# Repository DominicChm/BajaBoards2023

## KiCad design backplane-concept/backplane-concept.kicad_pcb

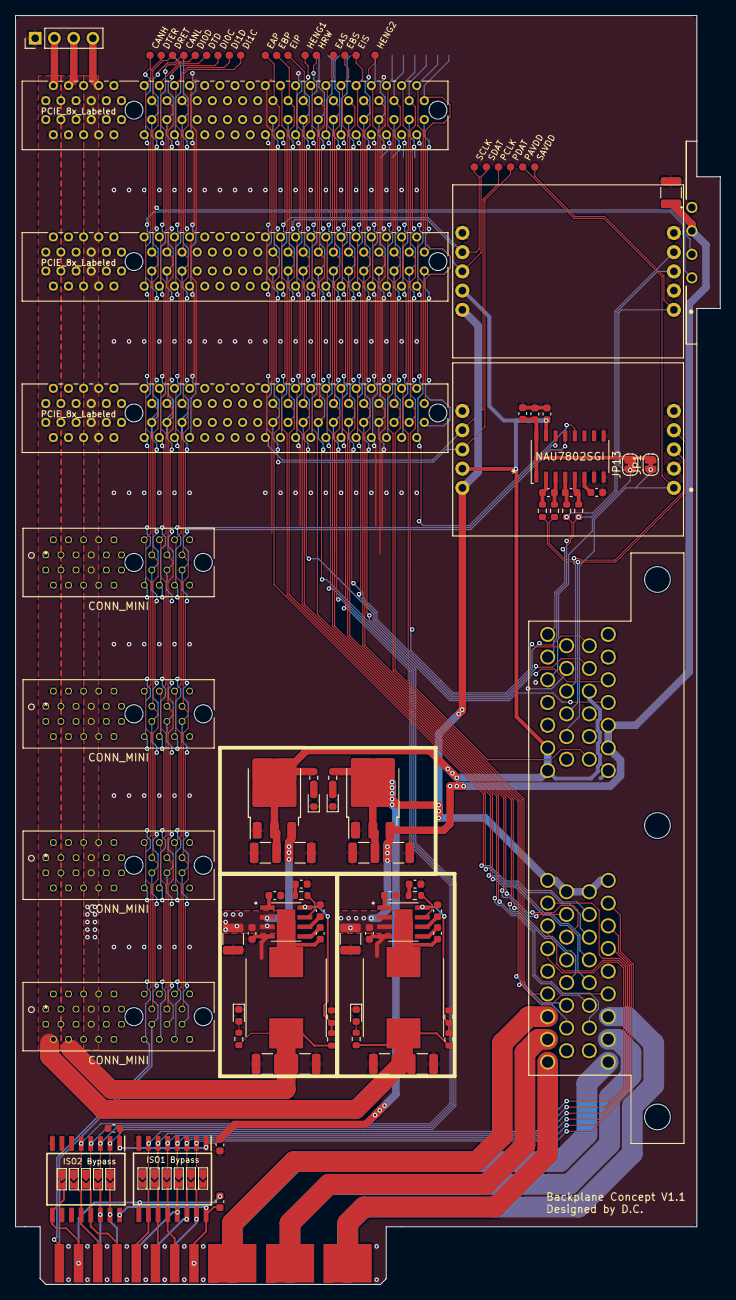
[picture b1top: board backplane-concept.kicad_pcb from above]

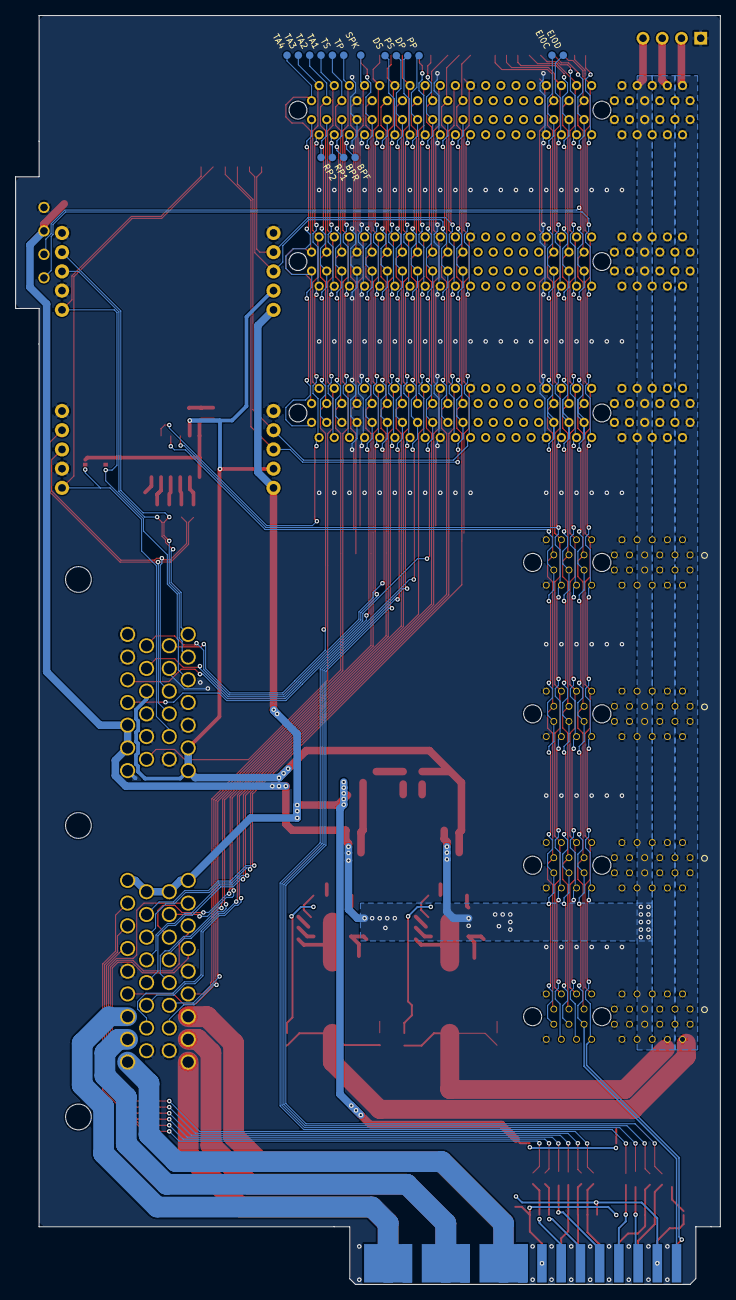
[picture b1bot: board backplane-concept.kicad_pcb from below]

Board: 2 copper layers, 93.1 x 167.6 mm, 124 parts (18 on the bottom side), 109 nets.

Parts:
C1, C3, C16, C21: 1uF; C_0603_1608Metric
C2, C4, C5, C6, C13, C22, C25, C26, C28, C29, C31: 0.1uF; C_0603_1608Metric
C7, C8, C9, C10, C12, C14, C15, C18, C23, C24, C27: 22uF; C_1210_3225Metric
C11, C20: 47nF; C_0603_1608Metric
C17, C19: 1.8nF; C_0603_1608Metric
D1: 3V3A; LED_0603_1608Metric
D2: 5VA; LED_0603_1608Metric
D3: 5V; LED_0603_1608Metric
D4: 3V3; LED_0603_1608Metric
IC1, IC2: ISO6760DWR; SOIC127P1030X265-16N
J1: ECVT I/O; 64734271
J2, J3, J4: PCIE_8x_Labeled; 9-1734774-5
J5, J6, J7, J8: CONN_MINI; 10018784-10200TLF
J10: 5-5530843-3-EDGE
J11: 1-967657-1; 19676571
J12: POWER; PinHeader_1x04_P2.54mm_Vertical
JP1: AVDD_P; SolderJumper-2_P1.3mm_Bridged_RoundedPad1.0x1.5mm
JP2, JP3, JP4, JP5, JP6, JP7, JP8, JP9, JP10, JP11, JP12: SolderJumper_2_Open; JMP_Small
JP13: AVDD_S; SolderJumper-2_P1.3mm_Bridged_RoundedPad1.0x1.5mm
L1, L2: 3.8uH; L_Taiyo-Yuden_NR-10050_9.8x10.0mm_HandSoldering
R1, R2, R3, R4: 47; R_0603_1608Metric
R5: 14.7K; R_0603_1608Metric
R6: 110K; R_0603_1608Metric
R7, R10: 15K; R_0603_1608Metric
R8: 10K; R_0603_1608Metric
R9: 67.5K; R_0603_1608Metric
R12, R15: 130; R_0603_1608Metric
R13, R14: 300; R_0603_1608Metric
TP1: PCLK; TestPoint_Pad_D1.0mm
TP2: PDAT; TestPoint_Pad_D1.0mm
TP3: SCLK; TestPoint_Pad_D1.0mm
TP4: SDAT; TestPoint_Pad_D1.0mm
TP5: SAVDD; TestPoint_Pad_D1.0mm
TP6: PAVDD; TestPoint_Pad_D1.0mm
TP12: HENG1; TestPoint_Pad_D1.0mm
TP13: HENG2; TestPoint_Pad_D1.0mm
TP14: BPF; TestPoint_Pad_D1.0mm
TP15: BPR; TestPoint_Pad_D1.0mm
TP16: RP1; TestPoint_Pad_D1.0mm
TP17: RP2; TestPoint_Pad_D1.0mm
TP18: HRW; TestPoint_Pad_D1.0mm
TP19: PP; TestPoint_Pad_D1.0mm
TP20: DP; TestPoint_Pad_D1.0mm
TP21: PS; TestPoint_Pad_D1.0mm
TP22: DS; TestPoint_Pad_D1.0mm
TP23: TP; TestPoint_Pad_D1.0mm
TP24: TS; TestPoint_Pad_D1.0mm
TP25: TA1; TestPoint_Pad_D1.0mm
TP26: TA2; TestPoint_Pad_D1.0mm
TP27: TA3; TestPoint_Pad_D1.0mm
TP28: TA4; TestPoint_Pad_D1.0mm
TP29: SPK; TestPoint_Pad_D1.0mm
TP30: EAS; TestPoint_Pad_D1.0mm
TP31: EBS; TestPoint_Pad_D1.0mm
TP32: EIS; TestPoint_Pad_D1.0mm
TP33: EAP; TestPoint_Pad_D1.0mm
TP34: EBP; TestPoint_Pad_D1.0mm
TP35: EIP; TestPoint_Pad_D1.0mm
TP36: DI1C; TestPoint_Pad_D1.0mm
TP37: DI1D; TestPoint_Pad_D1.0mm
TP38: DI0D; TestPoint_Pad_D1.0mm
TP39: DI0C; TestPoint_Pad_D1.0mm
TP40: CANH; TestPoint_Pad_D1.0mm
TP41: CANL; TestPoint_Pad_D1.0mm
TP42: EI0D; TestPoint_Pad_D1.0mm
TP43: EI0C; TestPoint_Pad_D1.0mm
TP44: DRET; TestPoint_Pad_D1.0mm
TP45: DTD; TestPoint_Pad_D1.0mm
TP46: DTER; TestPoint_Pad_D1.0mm
U1: PRIMARY; SPARKFUN_SEN-13879
U2: SECONDARY; SPARKFUN_SEN-13879
U3: NAU7802SGI
U6: 5V Reg; AOZ6605PI-1
U7: AMS1117CD-5.0; TO-252-3_TabPin2
U8: 3.3V Reg; AOZ6605PI-1
U9: AMS1117CD-3.3; TO-252-3_TabPin2

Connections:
+3.3VA: C1.1, C10.1, J1.B10, J1.B25, J1.B26, R12.1, U1.9 (VCC), U2.9 (VCC), U3.15 (DVDD), U9.2 (VO)
+3V3: C23.1, C24.1, J2.A4 (+3V3), J2.A5 (+3V3), J2.A6 (+3V3), J2.B4 (+3V3), J2.B5 (+3V3), J2.B6 (+3V3), J3.A4 (+3V3), J3.A5 (+3V3), J3.A6 (+3V3), J3.B4 (+3V3), J3.B5 (+3V3), J3.B6 (+3V3), J4.A4 (+3V3), J4.A5 (+3V3), J4.A6 (+3V3), J4.B4 (+3V3), J4.B5 (+3V3), J4.B6 (+3V3), J5.A4 (+3V3), J5.A5 (+3V3), J5.A6 (+3V3), J5.B4 (+3V3), J5.B5 (+3V3), J5.B6 (+3V3), J6.A4 (+3V3), J6.A5 (+3V3), J6.A6 (+3V3), J6.B4 (+3V3), J6.B5 (+3V3), J6.B6 (+3V3), J7.A4 (+3V3), J7.A5 (+3V3), J7.A6 (+3V3), J7.B4 (+3V3), J7.B5 (+3V3), J7.B6 (+3V3), J8.A4 (+3V3), J8.A5 (+3V3), J8.A6 (+3V3), J8.B4 (+3V3), J8.B5 (+3V3), J8.B6 (+3V3), J12.3, L2.2, R9.1, R15.1
+5V: C14.1, C15.1, J2.A1 (+5V), J2.A2 (+5V), J2.A3 (+5V), J2.B1 (+5V), J2.B2 (+5V), J2.B3 (+5V), J3.A1 (+5V), J3.A2 (+5V), J3.A3 (+5V), J3.B1 (+5V), J3.B2 (+5V), J3.B3 (+5V), J4.A1 (+5V), J4.A2 (+5V), J4.A3 (+5V), J4.B1 (+5V), J4.B2 (+5V), J4.B3 (+5V), J5.A1 (+5V), J5.A2 (+5V), J5.A3 (+5V), J5.B1 (+5V), J5.B2 (+5V), J5.B3 (+5V), J6.A1 (+5V), J6.A2 (+5V), J6.A3 (+5V), J6.B1 (+5V), J6.B2 (+5V), J6.B3 (+5V), J7.A1 (+5V), J7.A2 (+5V), J7.A3 (+5V), J7.B1 (+5V), J7.B2 (+5V), J7.B3 (+5V), J8.A1 (+5V), J8.A2 (+5V), J8.A3 (+5V), J8.B1 (+5V), J8.B2 (+5V), J8.B3 (+5V), J12.2, L1.2, R6.1, R14.1
+5VA: C8.1, C28.1, C31.1, IC1.1 (VCC1), IC2.1 (VCC1), J1.A1, J1.A10, J1.A18, J1.A26, R13.1, U1.10 (VDD), U2.10 (VDD), U7.2 (VO)
+8V: C7.1, C9.1, C12.1, C18.1, C25.1, C26.1, C27.1, J1.B5, J1.B6, J2.A7 (VBATT), J2.A8 (VBATT), J2.B7 (VBATT), J2.B8 (VBATT), J3.A7 (VBATT), J3.A8 (VBATT), J3.B7 (VBATT), J3.B8 (VBATT), J4.A7 (VBATT), J4.A8 (VBATT), J4.B7 (VBATT), J4.B8 (VBATT), J5.A7 (VBATT), J5.A8 (VBATT), J5.B7 (VBATT), J5.B8 (VBATT), J6.A7 (VBATT), J6.A8 (VBATT), J6.B7 (VBATT), J6.B8 (VBATT), J7.A7 (VBATT), J7.A8 (VBATT), J7.B7 (VBATT), J7.B8 (VBATT), J8.A7 (VBATT), J8.A8 (VBATT), J8.B7 (VBATT), J8.B8 (VBATT), J11.2 (VBATT), J12.4, U6.2 (EN), U6.3 (VIN), U7.3 (VI), U8.2 (EN), U8.3 (VIN), U9.3 (VI)
/DIR_P_ISO: IC2.14 (OUTB), J10.A15 (PWM_P), JP10.2 (B)
/DIR_S_ISO: IC2.12 (OUTD), J10.B15 (PWM_S), JP12.2 (B)
/HALL1_P_ISO: IC1.15 (OUTA), J10.A11 (HALL1_P), JP2.2 (B)
/HALL1_S_ISO: IC1.12 (OUTD), J10.B11 (HALL1_S), JP5.2 (B)
/HALL2_P_ISO: IC1.14 (OUTB), J10.A12 (HALL2_P), JP3.2 (B)
/HALL2_S_ISO: IC1.11 (OUTE), J10.B12 (HALL2_S), JP6.2 (B)
/HALL3_P_ISO: IC1.13 (OUTC), J10.A13 (HALL3_P), JP4.2 (B)
/HALL3_S_ISO: IC1.10 (OUTF), J10.B13 (HALL3_S), JP7.2 (B)
/PWM_P_ISO: IC2.15 (OUTA), J10.A14 (DIR_P), JP9.2 (B)
/PWM_S_ISO: IC2.13 (OUTC), J10.B14 (DIR_S), JP11.2 (B)
/VDD_ISO: C29.1, IC1.16 (VCC2), IC2.16 (VCC2), J10.A10 (VDD), J10.B10 (VDD)
/VSS_ISO: C29.2, IC1.9 (GND2), IC2.9 (GND2), J10.A16 (VSS), J10.B16 (VSS), JP8.2 (B)
ADC_IRQ: J2.B48, J3.B48, J4.B48, U3.12 (DRDY)
AVDD_P: J1.B18, JP1.1 (A), TP6.1, U1.1 (RED)
AVDD_S: J1.B22, JP13.1 (A), TP5.1, U2.1 (RED)
BP_FRONT: J2.B44 (BP_FRONT), J3.B44 (BP_FRONT), J4.B44 (BP_FRONT), TP14.1
BP_REAR: J2.B45 (BP_REAR), J3.B45 (BP_REAR), J4.B45 (BP_REAR), TP15.1
CAN_H: J2.B12 (CAN_H), J3.B12 (CAN_H), J4.B12 (CAN_H), J5.B12 (CAN_H), J6.B12 (CAN_H), J7.B12 (CAN_H), J8.B12 (CAN_H), J10.B17 (CANH), J11.4 (CANH), TP40.1
CAN_L: J2.B13 (CAN_L), J3.B13 (CAN_L), J4.B13 (CAN_L), J5.B13 (CAN_L), J6.B13 (CAN_L), J7.B13 (CAN_L), J8.B13 (CAN_L), J10.A17 (CANL), J11.3 (CANL), TP41.1
DAQ_RX0_ECVT_TX0: J2.A13 (DAQ_RX0_ECVT_TX0), J3.A13 (DAQ_RX0_ECVT_TX0), J4.A13 (DAQ_RX0_ECVT_TX0), J5.A13 (DAQ_RX0_ECVT_TX0), J6.A13 (DAQ_RX0_ECVT_TX0), J7.A13 (DAQ_RX0_ECVT_TX0), J8.A13 (DAQ_RX0_ECVT_TX0), TP44.1
DAQ_TX0_ECVT_RX0: J2.A12 (DAQ_TX0_ECVT_RX0), J3.A12 (DAQ_TX0_ECVT_RX0), J4.A12 (DAQ_TX0_ECVT_RX0), J5.A12 (DAQ_TX0_ECVT_RX0), J6.A12 (DAQ_TX0_ECVT_RX0), J7.A12 (DAQ_TX0_ECVT_RX0), J8.A12 (DAQ_TX0_ECVT_RX0), TP46.1
DAQ_TX1_DATA: J2.A14 (DAQ_TX1_DATA), J3.A14 (DAQ_TX1_DATA), J4.A14 (DAQ_TX1_DATA), J5.A14 (DAQ_TX1_DATA), J6.A14 (DAQ_TX1_DATA), J7.A14 (DAQ_TX1_DATA), J8.A14 (DAQ_TX1_DATA), TP45.1
DIR_P: IC2.3 (INB), J2.B36 (DIR_P), J3.B36 (DIR_P), J4.B36 (DIR_P), JP10.1 (A), TP20.1
DIR_S: IC2.5 (IND), J2.B38 (DIR_S), J3.B38 (DIR_S), J4.B38 (DIR_S), JP12.1 (A), TP22.1
ENCA_P: J1.A11, J2.A29 (ENCA_P), J3.A29 (ENCA_P), J4.A29 (ENCA_P), TP33.1
ENCA_S: J1.A19, J2.A36 (ENCA_S), J3.A36 (ENCA_S), J4.A36 (ENCA_S), TP30.1
ENCB_P: J1.A13, J2.A31 (ENCB_P), J3.A31 (ENCB_P), J4.A31 (ENCB_P), TP34.1
ENCB_S: J1.A21, J2.A38 (ENCB_S), J3.A38 (ENCB_S), J4.A38 (ENCB_S), TP31.1
ENCI_P: J1.A15, J2.A33 (ENCI_P), J3.A33 (ENCI_P), J4.A33 (ENCI_P), TP35.1
ENCI_S: J1.A23, J2.A40 (ENCI_S), J3.A40 (ENCI_S), J4.A40 (ENCI_S), TP32.1
GND: C1.2, C2.2, C3.2, C6.2, C7.2, C8.2, C9.2, C10.2, C11.2, C12.2, C14.2, C15.2, C16.2, C17.2, C18.2, C19.2, C20.2, C21.2, C23.2, C24.2, C25.2, C26.2, C27.2, C28.2, C31.2, D1.1 (K), D2.1 (K), D3.1 (K), D4.1 (K), IC1.8 (GND1), IC2.8 (GND1), J1.A5, J1.A17, J1.A25, J1.A30, J1.B1, J1.B2, J1.B7, J1.B11, J1.B12, J1.B15, J1.B19, J1.B23, J1.B24, J2.A9 (GND), J2.A10 (GND), J2.A11 (GND), J2.A15 (GND), J2.A18 (GND), J2.A28 (GND), J2.A35 (GND), J2.A43 (GND), J2.B9 (GND), J2.B10 (GND), J2.B11 (GND), J2.B18 (GND), J2.B32 (GND), J2.B42 (GND), J2.B43 (GND), J3.A9 (GND), J3.A10 (GND), J3.A11 (GND), J3.A15 (GND), J3.A18 (GND), J3.A28 (GND), J3.A35 (GND), J3.A43 (GND), J3.B9 (GND), J3.B10 (GND), J3.B11 (GND), J3.B18 (GND), J3.B32 (GND), J3.B42 (GND), J3.B43 (GND), J4.A9 (GND), J4.A10 (GND), J4.A11 (GND), J4.A15 (GND), J4.A18 (GND), J4.A28 (GND), J4.A35 (GND), J4.A43 (GND), J4.B9 (GND), J4.B10 (GND), J4.B11 (GND), J4.B18 (GND), J4.B32 (GND), J4.B42 (GND), J4.B43 (GND), J5.A9 (GND), J5.A10 (GND), J5.A11 (GND), J5.A15 (GND), J5.A18 (GND), J5.B9 (GND), J5.B10 (GND), J5.B11 (GND), J5.B18 (GND), J6.A9 (GND), J6.A10 (GND), J6.A11 (GND), J6.A15 (GND), J6.A18 (GND), J6.B9 (GND), J6.B10 (GND), J6.B11 (GND), J6.B18 (GND), J7.A9 (GND), J7.A10 (GND), J7.A11 (GND), J7.A15 (GND), J7.A18 (GND), J7.B9 (GND), J7.B10 (GND), J7.B11 (GND), J7.B18 (GND), J8.A9 (GND), J8.A10 (GND), J8.A11 (GND), J8.A15 (GND), J8.A18 (GND), J8.B9 (GND), J8.B10 (GND), J8.B11 (GND), J8.B18 (GND), J11.1 (GND), J12.1, JP8.1 (A), R7.2, R10.2, U1.2 (BLK), U1.5 (YLW), U1.6 (GND), U2.2 (BLK), U2.5 (YLW), U2.6 (GND), U3.7 (REFN), U3.8 (AVSS), U3.9 (DVSS), U6.4 (GND), U7.1 (GND), U8.4 (GND), U9.1 (GND)
HALL1_P: IC1.2 (INA), J1.A2, JP2.1 (A)
HALL1_S: IC1.5 (IND), J1.A27, JP5.1 (A)
HALL2_P: IC1.3 (INB), J1.A3, JP3.1 (A)
HALL2_S: IC1.6 (INE), J1.A28, JP6.1 (A)
HALL3_P: IC1.4 (INC), J1.A4, JP4.1 (A)
HALL3_S: IC1.7 (INF), J1.A29, JP7.1 (A)
HALL_ENG1: J1.B3, J2.B33 (HALL_ENG1), J3.B33 (HALL_ENG1), J4.B33 (HALL_ENG1), TP12.1
HALL_ENG2: J1.B4, J2.B41 (HALL_ENG2), J3.B41 (HALL_ENG2), J4.B41 (HALL_ENG2), TP13.1
HALL_RW: J2.B34 (HALL_RW), J3.B34 (HALL_RW), J4.B34 (HALL_RW), TP18.1
I2C0_DAQ_SCL: J2.B15 (I2C0_DAQ_SCL), J3.B15 (I2C0_DAQ_SCL), J4.B15 (I2C0_DAQ_SCL), J5.B15 (I2C0_DAQ_SCL), J6.B15 (I2C0_DAQ_SCL), J7.B15 (I2C0_DAQ_SCL), J8.B15 (I2C0_DAQ_SCL), TP39.1
I2C0_DAQ_SDA: J2.B14 (I2C0_DAQ_SDA), J3.B14 (I2C0_DAQ_SDA), J4.B14 (I2C0_DAQ_SDA), J5.B14 (I2C0_DAQ_SDA), J6.B14 (I2C0_DAQ_SDA), J7.B14 (I2C0_DAQ_SDA), J8.B14 (I2C0_DAQ_SDA), TP38.1
I2C0_ECVT_SCL: J2.B17 (I2C0_ECVT_SCL), J3.B17 (I2C0_ECVT_SCL), J4.B17 (I2C0_ECVT_SCL), J5.B17 (I2C0_ECVT_SCL), J6.B17 (I2C0_ECVT_SCL), J7.B17 (I2C0_ECVT_SCL), J8.B17 (I2C0_ECVT_SCL), TP43.1, U3.13 (SCLK)
I2C0_ECVT_SDA: J2.B16 (I2C0_ECVT_SDA), J3.B16 (I2C0_ECVT_SDA), J4.B16 (I2C0_ECVT_SDA), J5.B16 (I2C0_ECVT_SDA), J6.B16 (I2C0_ECVT_SDA), J7.B16 (I2C0_ECVT_SDA), J8.B16 (I2C0_ECVT_SDA), TP42.1, U3.14 (SDIO)
I2C1_DAQ_SCL: J2.A17 (I2C1_DAQ_SCL), J3.A17 (I2C1_DAQ_SCL), J4.A17 (I2C1_DAQ_SCL), J5.A17 (I2C1_DAQ_SCL), J6.A17 (I2C1_DAQ_SCL), J7.A17 (I2C1_DAQ_SCL), J8.A17 (I2C1_DAQ_SCL), TP36.1
I2C1_DAQ_SDA: J2.A16 (I2C1_DAQ_SDA), J3.A16 (I2C1_DAQ_SDA), J4.A16 (I2C1_DAQ_SDA), J5.A16 (I2C1_DAQ_SDA), J6.A16 (I2C1_DAQ_SDA), J7.A16 (I2C1_DAQ_SDA), J8.A16 (I2C1_DAQ_SDA), TP37.1
I2C1_ECVT_EXT_SCL: J1.B9, J2.B40 (I2C1_ECVT_EXT_SCL), J3.B40 (I2C1_ECVT_EXT_SCL), J4.B40 (I2C1_ECVT_EXT_SCL)
I2C1_ECVT_EXT_SDA: J1.B8, J2.B39 (I2C1_ECVT_EXT_SDA), J3.B39 (I2C1_ECVT_EXT_SDA), J4.B39 (I2C1_ECVT_EXT_SDA)
IN+_P: J1.B16, R1.1, U1.3 (WHT)
IN+_S: J1.B20, R4.1, U2.3 (WHT)
IN-_P: J1.B17, R2.1, U1.4 (GRN)
IN-_S: J1.B21, R3.1, U2.4 (GRN)
LOADC_CLK_P: J2.B28 (LOADC_CLK_P), J3.B28 (LOADC_CLK_P), J4.B28 (LOADC_CLK_P), TP1.1, U1.7 (CLK)
LOADC_CLK_S: J2.B30 (LOADC_CLK_S), J3.B30 (LOADC_CLK_S), J4.B30 (LOADC_CLK_S), TP3.1, U2.7 (CLK)
LOADC_DAT_P: J2.B29 (LOADC_DAT_P), J3.B29 (LOADC_DAT_P), J4.B29 (LOADC_DAT_P), TP2.1, U1.8 (DAT)
LOADC_DAT_S: J2.B31 (LOADC_DAT_S), J3.B31 (LOADC_DAT_S), J4.B31 (LOADC_DAT_S), TP4.1, U2.8 (DAT)
MOT1_P: J1.A7, J10.A1 (MOT1_P), J10.A2, J10.A3
MOT1_S: J1.A32, J10.B7 (MOT3_S), J10.B8, J10.B9
MOT2_P: J1.A8, J10.A4 (MOT2_P), J10.A5, J10.A6
MOT2_S: J1.A33, J10.B4 (MOT2_S), J10.B5, J10.B6 (MOT3_S)
MOT3_P: J1.A9, J10.A7 (MOT3_P), J10.A8, J10.A9
MOT3_S: J1.A34, J10.B1 (MOT1_S), J10.B2, J10.B3
unnamed: C17.1, R5.2
unnamed: C19.1, R8.2
unnamed: D1.2 (A), R12.2
unnamed: D2.2 (A), R13.2
unnamed: D3.2 (A), R14.2
unnamed: D4.2 (A), R15.2
unnamed: J2.B49, J3.B49, J4.B49
unnamed: C2.1, C3.1, JP1.2 (B), JP13.2 (B), U3.1 (REFP), U3.16 (AVDD/LDO)
unnamed: C6.1, U3.6 (VBG)
unnamed: C4.1, R2.2, U3.2 (VIN1N)
unnamed: C4.2, R1.2, U3.3 (VIN1P)
unnamed: C5.1, R3.2, U3.4 (VIN2N)
unnamed: C5.2, R4.2, U3.5 (VIN2P)
unnamed: C13.1, U6.5 (BST)
unnamed: R5.1, U6.7 (COMP)
unnamed: R6.2, R7.1, U6.8 (FB)
unnamed: C13.2, L1.1, U6.9 (LX)
unnamed: C11.1, U6.1 (SS)
unnamed: C16.1, U6.6 (VCC)
unnamed: C22.1, U8.5 (BST)
unnamed: R8.1, U8.7 (COMP)
unnamed: R9.2, R10.1, U8.8 (FB)
unnamed: C22.2, L2.1, U8.9 (LX)
unnamed: C20.1, U8.1 (SS)
unnamed: C21.1, U8.6 (VCC)
PWM_P: IC2.2 (INA), J2.B35 (PWM_P), J3.B35 (PWM_P), J4.B35 (PWM_P), JP9.1 (A), TP19.1
PWM_S: IC2.4 (INC), J2.B37 (PWM_S), J3.B37 (PWM_S), J4.B37 (PWM_S), JP11.1 (A), TP21.1
RPOT1: J2.B46 (RPOT1), J3.B46 (RPOT1), J4.B46 (RPOT1), TP16.1
RPOT2: J2.B47 (RPOT2), J3.B47 (RPOT2), J4.B47 (RPOT2), TP17.1
SPARK: J2.A42 (SPARK), J3.A42 (SPARK), J4.A42 (SPARK), TP29.1
THERM_A1_CASE: J1.B13, J2.A46 (THERM_A1_CASE), J3.A46 (THERM_A1_CASE), J4.A46 (THERM_A1_CASE), TP25.1
THERM_A2_CASE: J1.B14, J2.A47 (THERM_A2_CASE), J3.A47 (THERM_A2_CASE), J4.A47 (THERM_A2_CASE), TP26.1
THERM_A3: J2.A48 (THERM_A3), J3.A48 (THERM_A3), J4.A48 (THERM_A3), TP27.1
THERM_A4: J2.A49 (THERM_A4), J3.A49 (THERM_A4), J4.A49 (THERM_A4), TP28.1
THERM_P: J1.A6, J2.A44 (THERM_P), J3.A44 (THERM_P), J4.A44 (THERM_P), TP23.1
THERM_S: J1.A31, J2.A45 (THERM_S), J3.A45 (THERM_S), J4.A45 (THERM_S), TP24.1
~ENCA_P: J1.A12, J2.A30 (~ENCA_P), J3.A30 (~ENCA_P), J4.A30 (~ENCA_P)
~ENCA_S: J1.A20, J2.A37 (~ENCA_S), J3.A37 (~ENCA_S), J4.A37 (~ENCA_S)
~ENCB_P: J1.A14, J2.A32 (~ENCB_P), J3.A32 (~ENCB_P), J4.A32 (~ENCB_P)
~ENCB_S: J1.A22, J2.A39 (~ENCB_S), J3.A39 (~ENCB_S), J4.A39 (~ENCB_S)
~ENCI_P: J1.A16, J2.A34 (~ENCI_P), J3.A34 (~ENCI_P), J4.A34 (~ENCI_P)
~ENCI_S: J1.A24, J2.A41 (~ENCI_S), J3.A41 (~ENCI_S), J4.A41 (~ENCI_S)

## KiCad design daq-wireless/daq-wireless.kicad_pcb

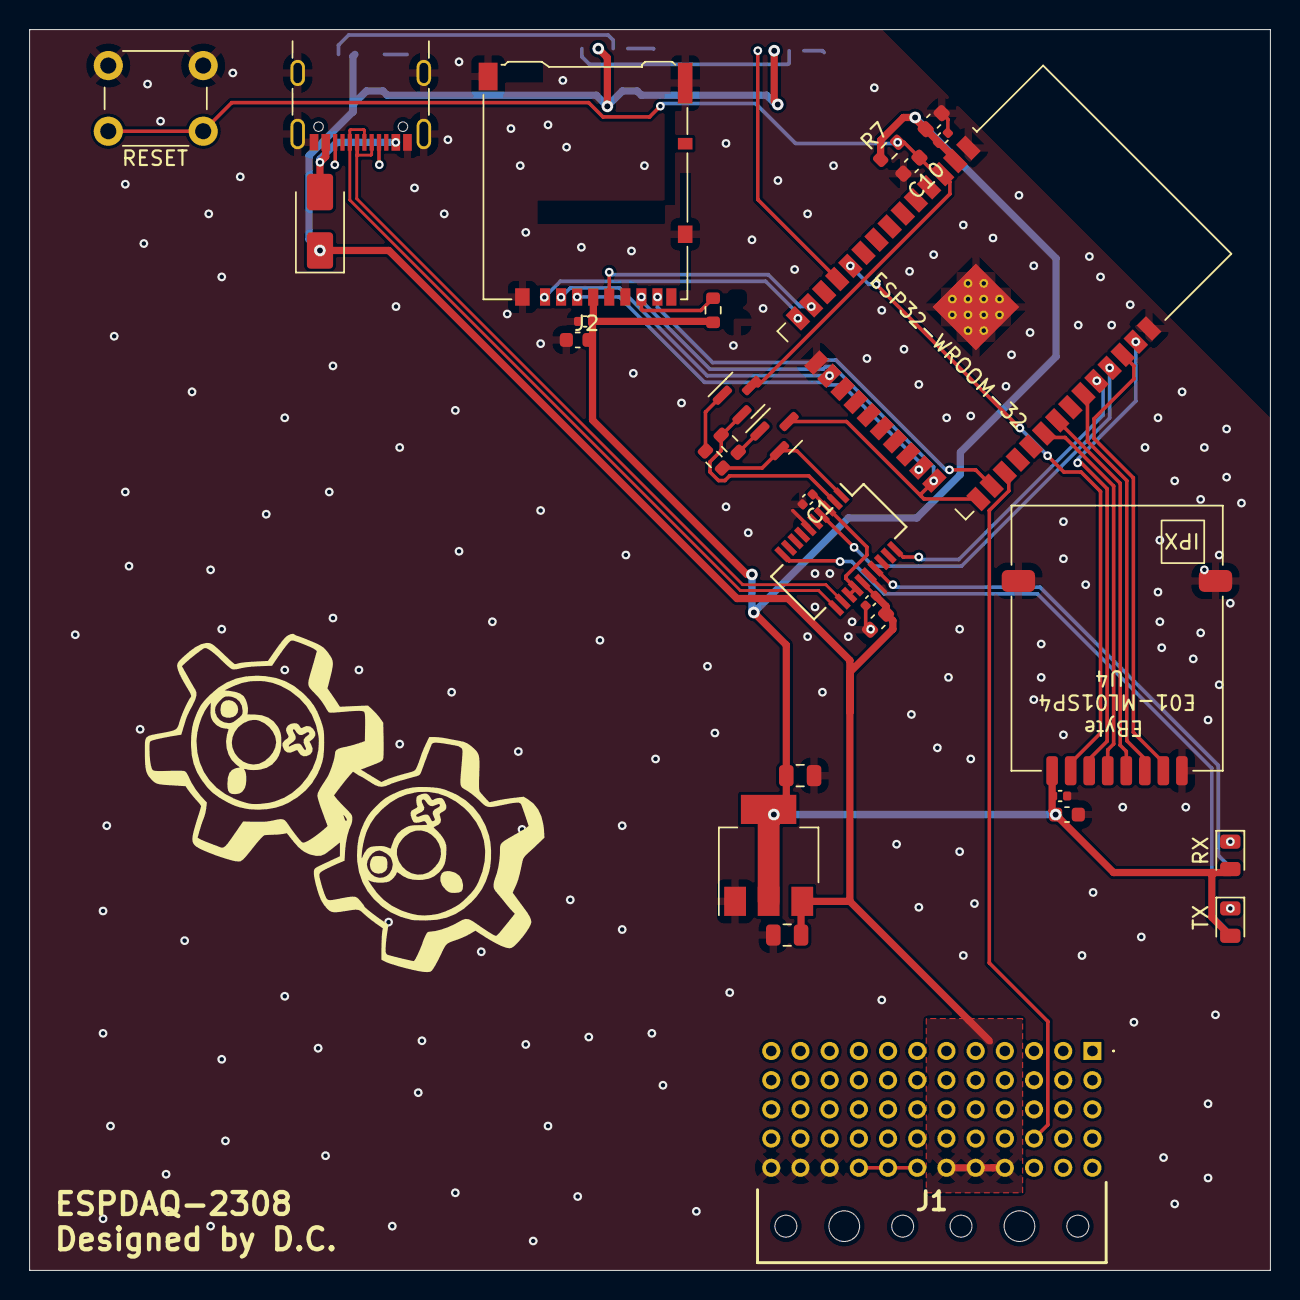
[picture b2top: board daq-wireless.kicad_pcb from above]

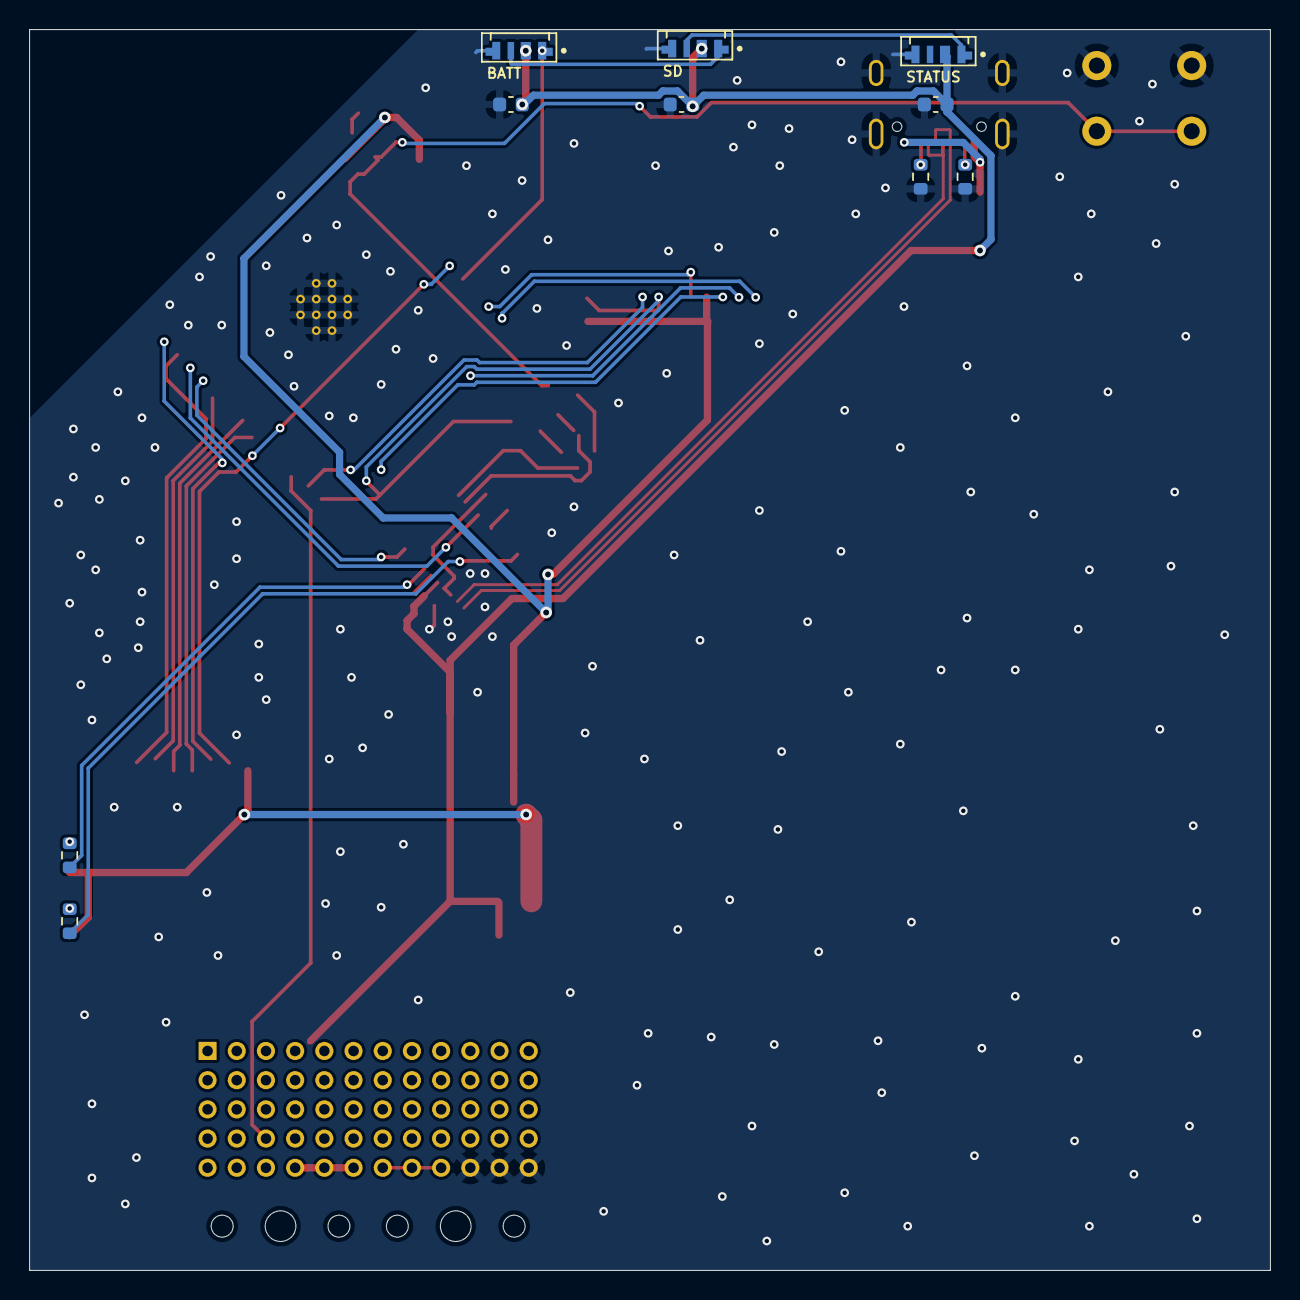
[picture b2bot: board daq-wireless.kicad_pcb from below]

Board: 2 copper layers, 85.0 x 85.0 mm, 39 parts (10 on the bottom side), 36 nets.

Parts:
C1, C3, C7, C9, C14: .1uF; C_0402_1005Metric
C2, C6, C8, C10, C11, C12, C13: 1uF; C_0603_1608Metric
C4, C5: 22uF; C_0805_2012Metric
C15: 10uF; C_0603_1608Metric
D1: D; D_SMA
D2: RX; D_0805_2012Metric
D3: TX; D_0805_2012Metric
D4: STATUS; LED_IN-PI42TASPRPGPB
D7: SD; LED_IN-PI42TASPRPGPB
D9: BATT; LED_IN-PI42TASPRPGPB
J1: 5223004-2; 52230042
J2: Micro_SD_Card; microSD_HC_Hirose_DM3AT-SF-PEJM5
J3: USB_C_Receptacle_USB2.0; USB_C_Receptacle_GCT_USB4105-xx-A_16P_TopMnt_Horizontal
Q1, Q2: MMBT3904; SOT-23
R1, R4, R7, R8: 10k; R_0603_1608Metric
R2, R3: 5.1k; R_0603_1608Metric
R5, R6: 1k; R_0603_1608Metric
SW1: RESET; SW_PUSH_6mm
U1: ESP32-WROOM-32
U2: AMS1117; SOT-223-3_TabPin2
U3: FT231XS; SSOP-20_3.9x8.7mm_P0.635mm
U4: Ebyte_E01-ML01SP4; Ebyte E01-ML01SP4

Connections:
+3V3: C5.1, C6.1, C7.1, C8.1, C9.1, C14.1, C15.1, D2.2 (A), D3.2 (A), J2.4 (VDD), R7.1, R8.1, U1.2 (VDD), U2.2 (VO), U4.1 (VCC)
+5V: C2.1, C3.1, C4.1, C11.1, C12.1, C13.1, D1.1 (K), D4.2 (VDD), D7.2 (VDD), D9.2 (VDD), J1.E4, J1.E5, J1.E6, U2.3 (VI), U3.15 (VCC)
/ARGB: D9.1 (DIN), U1.11 (IO26)
/D+: J3.A6 (D+), J3.B6 (D+), U3.11 (USBDP)
/D-: J3.A7 (D-), J3.B7 (D-), U3.12 (USBDM)
/DTR: Q2.2 (E), R1.2, U3.1 (~DTR)
/EN: C10.1, Q1.3 (C), R7.2, SW1.2, U1.3 (EN)
/IO0: J2.7 (DAT0), Q2.3 (C), R8.2, U1.24 (IO2), U1.25 (IO0)
/MISO: U1.33 (IO21), U4.6 (MISO)
/MOSI: U1.31 (IO19), U4.5 (MOSI)
/RADIO_CE: U1.10 (IO25), U4.2 (CE)
/RADIO_CS: U1.37 (IO23), U4.3 (CS)
/RADIO_IRQ: U1.36 (IO22), U4.7 (IRQ)
/RTS: Q1.2 (E), R4.2, U3.2 (~RTS)
/RXD: U1.35 (TXD0/IO1), U3.4 (RXD)
/SCK: U1.30 (IO18), U4.4 (SCK)
/SD1: J2.8 (DAT1), U1.26 (IO4)
/SD2: J2.1 (DAT2), U1.14 (IO12)
/SD3: J2.2 (DAT3/CD), U1.16 (IO13)
/SD_CLK: J2.5 (CLK), U1.13 (IO14)
/SD_CMD: J2.3 (CMD), U1.23 (IO15)
/TXD: U1.34 (RXD0/IO3), U3.20 (TXD)
CVT_TX_DAQ_RX: J1.D3, U1.27 (IO16)
GND: C1.2, C2.2, C3.2, C4.2, C5.2, C6.2, C7.2, C8.2, C9.2, C10.2, C11.2, C12.2, C13.2, C14.2, C15.2, D4.4 (GND), D7.4 (GND), D9.4 (GND), J1.E10, J1.E11, J1.E12, J2.6 (VSS), J2.11 (SHIELD), J3.A1 (GND), J3.A12 (GND), J3.B1 (GND), J3.B12 (GND), J3.S1 (SHIELD), R2.2, R3.2, SW1.1, U1.1 (GND), U1.15 (GND), U1.38 (GND), U1.39 (GND), U2.1 (ADJ), U3.6 (GND), U3.16 (GND), U4.8 (GND), U4.9 (GND), U4.10 (GND)
unnamed: D1.2 (A), J3.A4 (VBUS), J3.A9 (VBUS), J3.B4 (VBUS), J3.B9 (VBUS)
unnamed: D2.1 (K), R5.1
unnamed: D3.1 (K), R6.1
unnamed: D4.1 (DIN), D7.3 (DOUT)
unnamed: D7.1 (DIN), D9.3 (DOUT)
unnamed: J3.A5 (CC1), R3.1
unnamed: J3.B5 (CC2), R2.1
unnamed: Q1.1 (B), R1.1
unnamed: Q2.1 (B), R4.1
unnamed: C1.1, U3.3 (VCCIO), U3.13 (3V3OUT), U3.14 (~RESET)
unnamed: R5.2, U3.17 (CBUS1)
unnamed: R6.2, U3.10 (CBUS2)

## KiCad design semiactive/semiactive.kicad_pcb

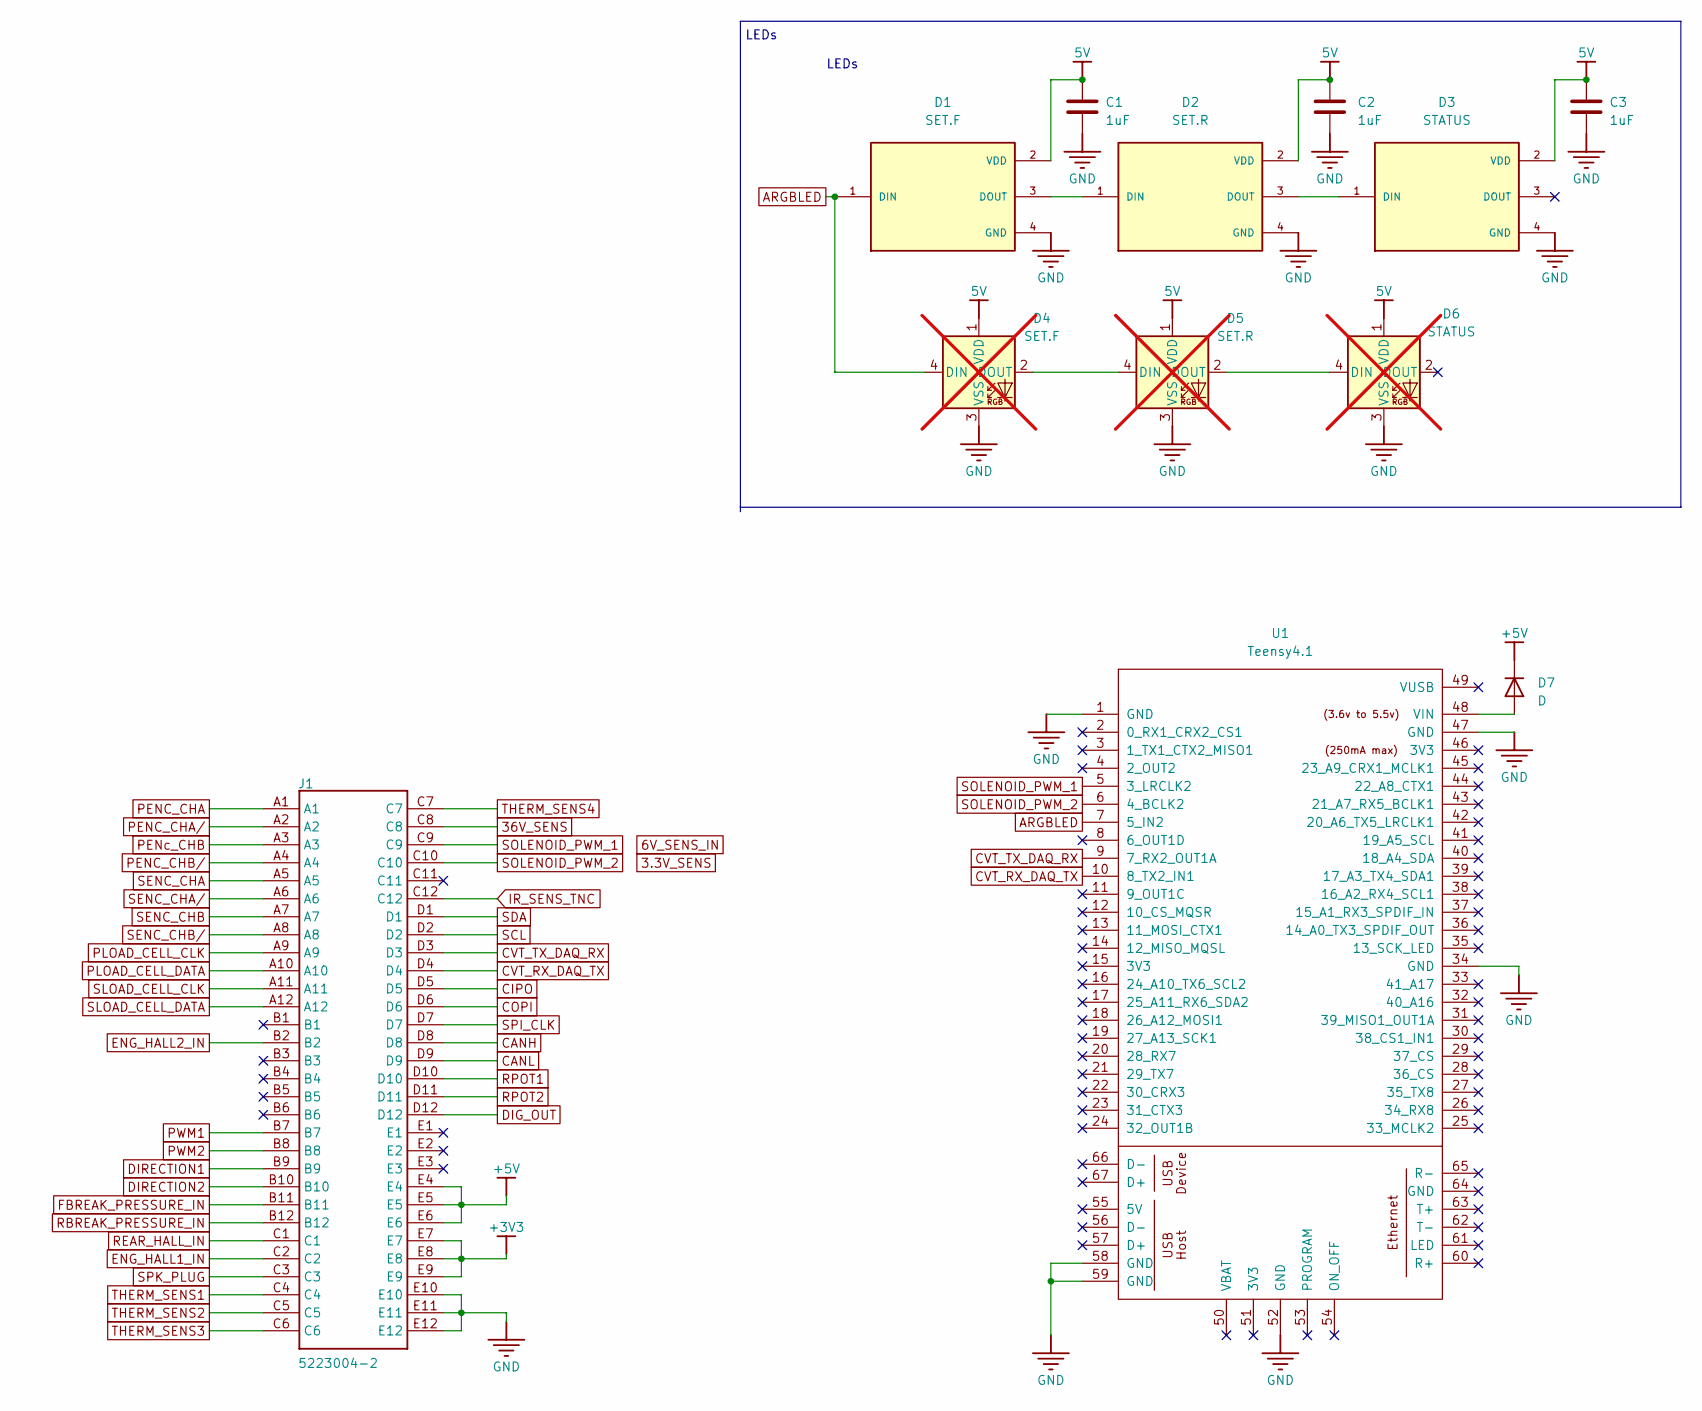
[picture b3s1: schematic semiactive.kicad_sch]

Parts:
C1, C2, C3: 1uF; C_0603_1608Metric
D1: SET.F; LED_IN-PI42TASPRPGPB; PARTREV Oct. 10, 2021
D2: SET.R; LED_IN-PI42TASPRPGPB; PARTREV Oct. 10, 2021
D3: STATUS; LED_IN-PI42TASPRPGPB; PARTREV Oct. 10, 2021
D4: SET.F; LED_WS2812B_PLCC4_5.0x5.0mm_P3.2mm; not fitted
D5: SET.R; LED_WS2812B_PLCC4_5.0x5.0mm_P3.2mm; not fitted
D6: STATUS; LED_WS2812B_PLCC4_5.0x5.0mm_P3.2mm; not fitted
D7: D; D_SMA
J1: 5223004-2; 52230042; MOUSER PART NUMBER 571-5223004-2
U1: Teensy4.1; Teensy41

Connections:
36V_SENS: J1.C8
+3V3: J1.E7, J1.E8, J1.E9
ARGBLED: D1.1 (DIN), D4.4 (DIN), U1.7 (5_IN2)
CANH: J1.D8
CANL: J1.D9
CIPO: J1.D5
COPI: J1.D6
CVT_RX_DAQ_TX: J1.D4, U1.10 (8_TX2_IN1)
CVT_TX_DAQ_RX: J1.D3, U1.9 (7_RX2_OUT1A)
DIG_OUT: J1.D12
DIRECTION1: J1.B9
DIRECTION2: J1.B10
ENG_HALL1_IN: J1.C2
ENG_HALL2_IN: J1.B2
FBREAK_PRESSURE_IN: J1.B11
GND: C1.2, C2.2, C3.2, D1.4 (GND), D2.4 (GND), D3.4 (GND), D4.3 (VSS), D5.3 (VSS), D6.3 (VSS), J1.E10, J1.E11, J1.E12, U1.1 (GND), U1.34 (GND), U1.47 (GND), U1.52 (GND), U1.58 (GND), U1.59 (GND)
IR_SENS_TNC: J1.C12
unnamed: D1.3 (DOUT), D2.1 (DIN)
unnamed: D2.3 (DOUT), D3.1 (DIN)
unnamed: D4.2 (DOUT), D5.4 (DIN)
unnamed: D5.2 (DOUT), D6.4 (DIN)
unnamed: D7.2 (A), U1.48 (VIN)
PENC_CHA: J1.A1
PENC_CHA/: J1.A2
PENC_CHB/: J1.A4
PENc_CHB: J1.A3
PLOAD_CELL_CLK: J1.A9
PLOAD_CELL_DATA: J1.A10
PWM1: J1.B7
PWM2: J1.B8
RBREAK_PRESSURE_IN: J1.B12
REAR_HALL_IN: J1.C1
RPOT1: J1.D10
RPOT2: J1.D11
SCL: J1.D2
SDA: J1.D1
SENC_CHA: J1.A5
SENC_CHA/: J1.A6
SENC_CHB: J1.A7
SENC_CHB/: J1.A8
SLOAD_CELL_CLK: J1.A11
SLOAD_CELL_DATA: J1.A12
SOLENOID_PWM_1: J1.C9, U1.5 (3_LRCLK2)
SOLENOID_PWM_2: J1.C10, U1.6 (4_BCLK2)
SPI_CLK: J1.D7
SPK_PLUG: J1.C3
THERM_SENS1: J1.C4
THERM_SENS2: J1.C5
THERM_SENS3: J1.C6
THERM_SENS4: J1.C7

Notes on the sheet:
LEDs
LEDs

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
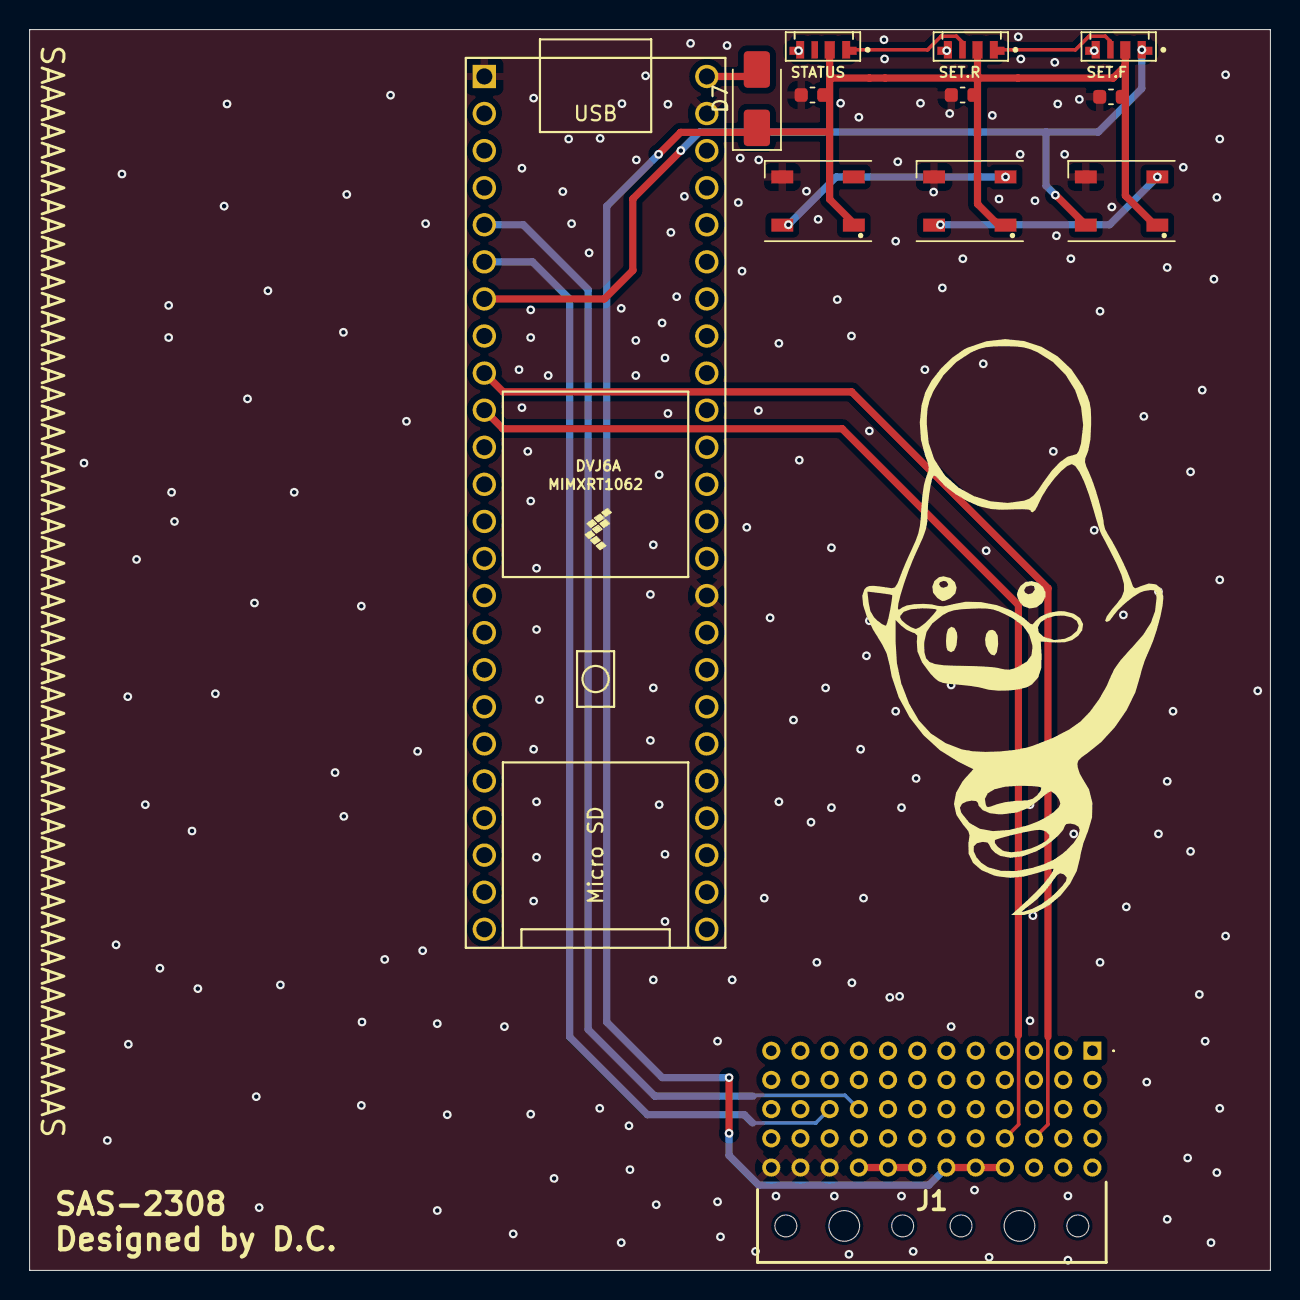
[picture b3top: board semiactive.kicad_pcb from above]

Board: 2 copper layers, 85.0 x 85.0 mm, 12 parts (0 on the bottom side), 13 nets.

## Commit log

2023-02-23 inital commit
2023-02-23 Wireless update
2023-02-23 Setup libs, scripts
2023-02-25 Create a few projects
2023-02-26 Route SAS board
2023-02-26 Aesthetic SAS updates
2023-02-26 SAS: Small changes
    Should be all routed and ready to go...
2023-02-27 Easter eggs
2023-02-27 Semiactive, DAQ-wireless updates (schem, board)
2023-02-27 Wireless DAQ routing
    Passes DRC
2023-02-28 DAQ updates
2023-02-28 Update semiactive ponkerman
2023-02-28 Critical ESPdaq fix
2023-02-28 Update SD symbol
2023-02-28 Change CE pin away from UART tx
2023-03-01 Quote update
2023-03-01 Generate gerbers
2023-03-09 Bugfix DAQ board
2023-03-22 Backplane Ideas
2023-03-22 Design PSUs, route bucks
2023-03-22 Add testpoints
2023-03-22 Route some test points
2023-03-22 More routing
2023-03-24 more roting
2023-03-25 Moar Routing
2023-04-10 Finish Routing
2023-04-10 TODO
    Holes,
    double check

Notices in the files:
parts and their libraries:
Copyright 2021 Accelerated Designs. All rights reserved.
